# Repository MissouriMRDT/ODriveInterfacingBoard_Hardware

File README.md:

# ODriveInterfacingBoard_Hardware

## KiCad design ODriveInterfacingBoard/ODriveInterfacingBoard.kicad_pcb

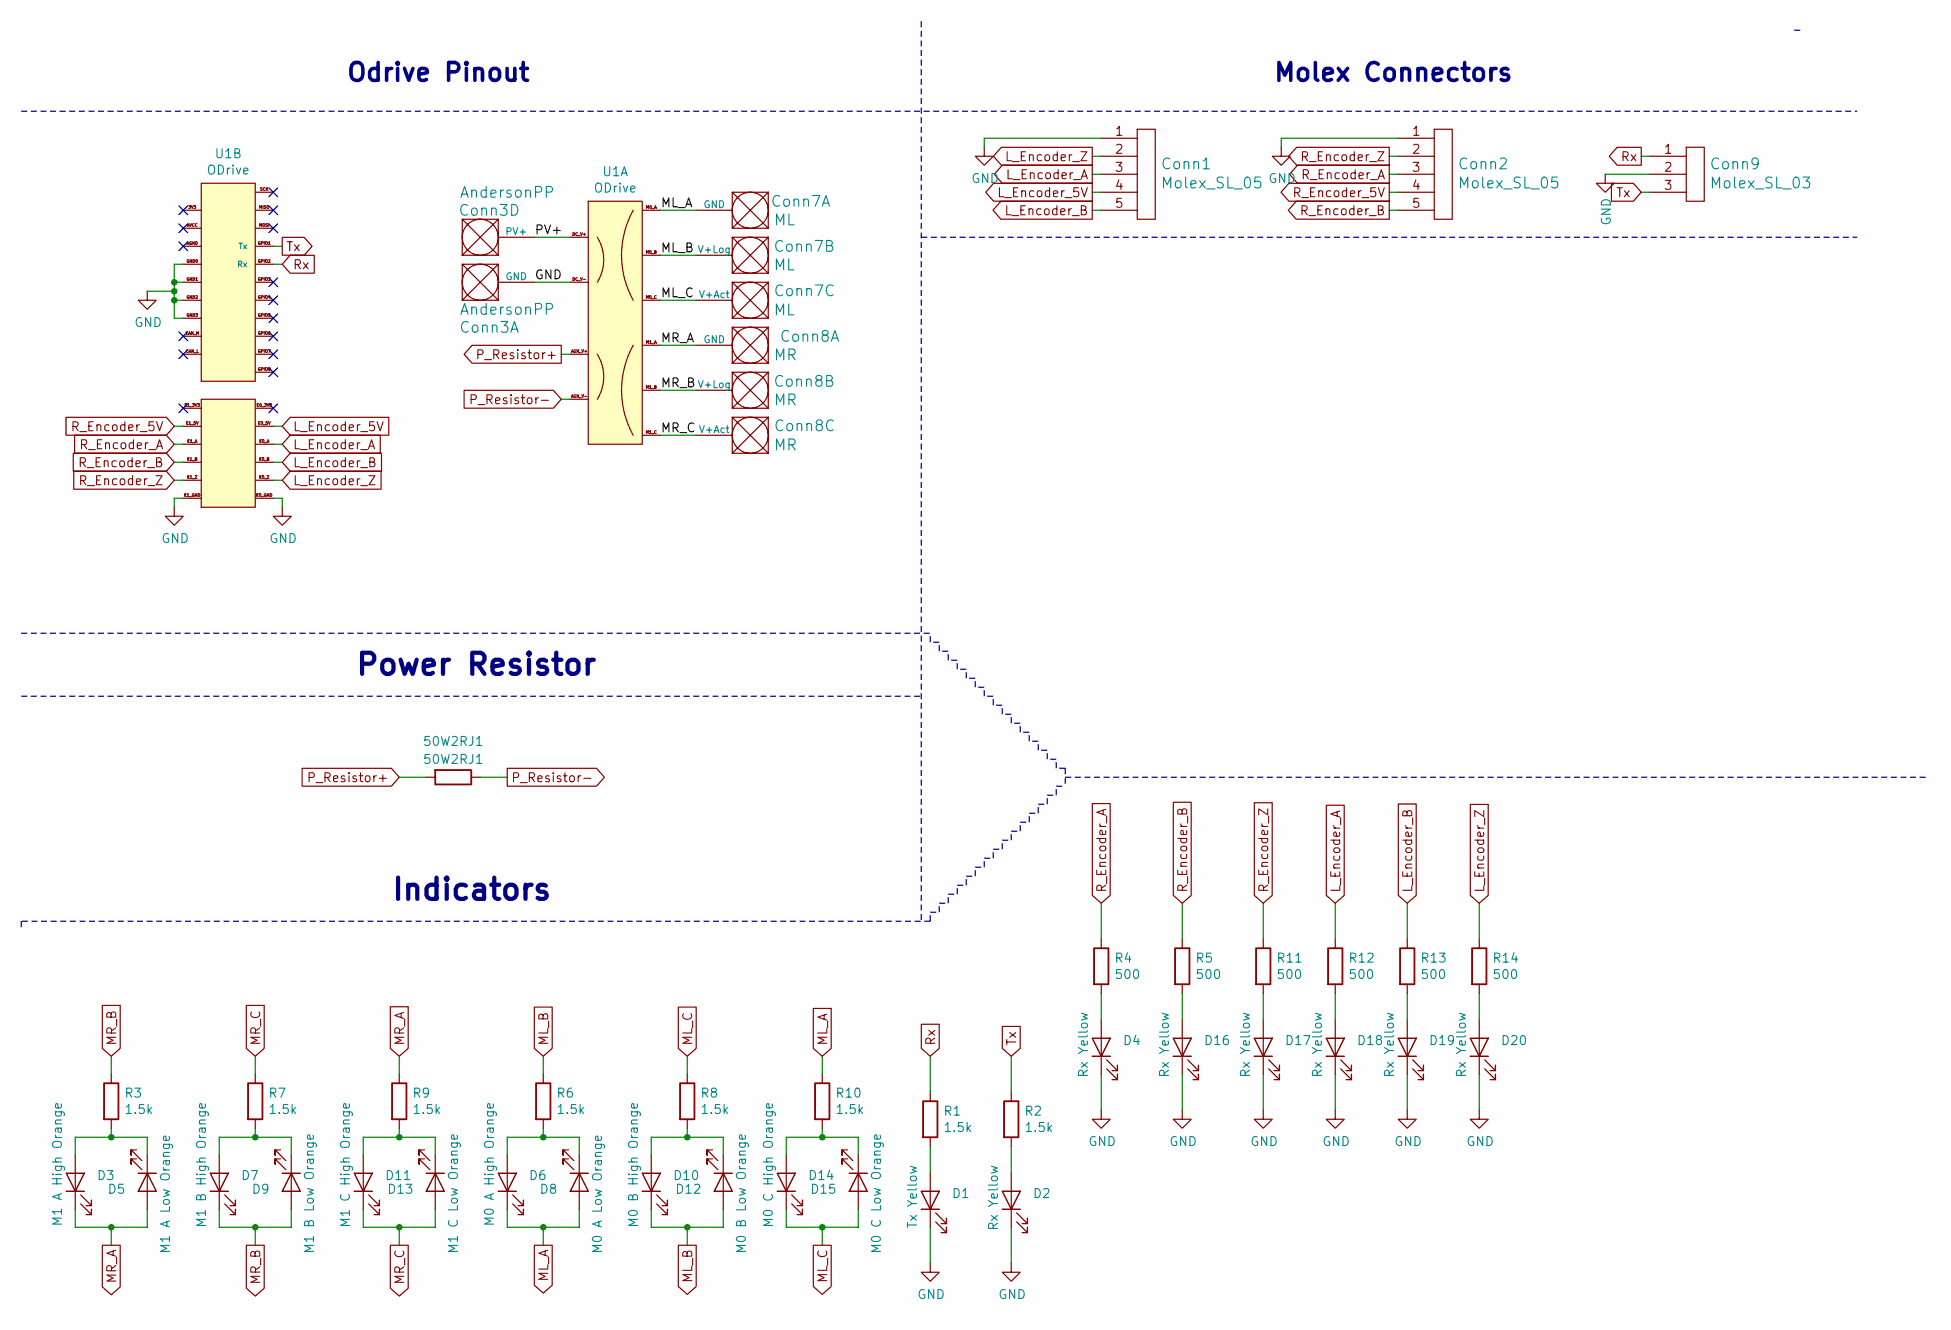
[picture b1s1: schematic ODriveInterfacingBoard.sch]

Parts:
50W2RJ1: 50W2RJ1; PowerResistorMounts
Conn1, Conn2: Molex_SL_05; MOLEX_SL_05_Horizontal
Conn3: AndersonPP; Anderson_2_Horizontal_Stacked
Conn7: ML; Anderson_3_Horizontal_Side_by_Side
Conn8: MR; Anderson_3_Horizontal_Side_by_Side
Conn9: Molex_SL_03; MOLEX_SL_03_Horizontal
D1: Tx Yellow; LED_0603_1608Metric_Pad1.05x0.95mm_HandSolder
D2, D4, D16, D17, D18, D19, D20: Rx Yellow; LED_0603_1608Metric_Pad1.05x0.95mm_HandSolder
D3: M1 A High Orange; LED_0603_1608Metric_Pad1.05x0.95mm_HandSolder
D5: M1 A Low Orange; LED_0603_1608Metric_Pad1.05x0.95mm_HandSolder
D6: M0 A High Orange; LED_0603_1608Metric_Pad1.05x0.95mm_HandSolder
D7: M1 B High Orange; LED_0603_1608Metric_Pad1.05x0.95mm_HandSolder
D8: M0 A Low Orange; LED_0603_1608Metric_Pad1.05x0.95mm_HandSolder
D9: M1 B Low Orange; LED_0603_1608Metric_Pad1.05x0.95mm_HandSolder
D10: M0 B High Orange; LED_0603_1608Metric_Pad1.05x0.95mm_HandSolder
D11: M1 C High Orange; LED_0603_1608Metric_Pad1.05x0.95mm_HandSolder
D12: M0 B Low Orange; LED_0603_1608Metric_Pad1.05x0.95mm_HandSolder
D13: M1 C Low Orange; LED_0603_1608Metric_Pad1.05x0.95mm_HandSolder
D14: M0 C High Orange; LED_0603_1608Metric_Pad1.05x0.95mm_HandSolder
D15: M0 C Low Orange; LED_0603_1608Metric_Pad1.05x0.95mm_HandSolder
R1, R2, R3, R6, R7, R8, R9, R10: 1.5k; R_0603_1608Metric_Pad1.05x0.95mm_HandSolder
R4, R5, R11, R12, R13, R14: 500; R_0603_1608Metric_Pad1.05x0.95mm_HandSolder
U1: ODrive; ODriveInterfacingBoard

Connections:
/PV+: Conn3.4 (PV+), U1.DC_V+
GND: Conn1.1, Conn2.1, Conn3.1 (GND), Conn9.2, D1.1 (K), D2.1 (K), D4.1 (K), D16.1 (K), D17.1 (K), D18.1 (K), D19.1 (K), D20.1 (K), U1.DC_V-, U1.E0_GND, U1.E1_GND, U1.GND0, U1.GND1, U1.GND2, U1.GND3
L_Encoder_5V: Conn1.4, U1.E0_5V
L_Encoder_A: Conn1.3, R12.1, U1.E0_A
L_Encoder_B: Conn1.5, R13.1, U1.E0_B
L_Encoder_Z: Conn1.2, R14.1, U1.E0_Z
ML_A: Conn7.1 (GND), D6.1 (K), D8.2 (A), R10.1, U1.M0_A
ML_B: Conn7.2 (V+Log), D10.1 (K), D12.2 (A), R6.1, U1.M0_B
ML_C: Conn7.3 (V+Act), D14.1 (K), D15.2 (A), R8.1, U1.M0_C
MR_A: Conn8.1 (GND), D3.1 (K), D5.2 (A), R9.1, U1.M1_A
MR_B: Conn8.2 (V+Log), D7.1 (K), D9.2 (A), R3.1, U1.M1_B
MR_C: Conn8.3 (V+Act), D11.1 (K), D13.2 (A), R7.1, U1.M1_C
unnamed: D1.2 (A), R1.2
unnamed: D2.2 (A), R2.2
unnamed: D3.2 (A), D5.1 (K), R3.2
unnamed: D4.2 (A), R4.2
unnamed: D6.2 (A), D8.1 (K), R6.2
unnamed: D7.2 (A), D9.1 (K), R7.2
unnamed: D10.2 (A), D12.1 (K), R8.2
unnamed: D11.2 (A), D13.1 (K), R9.2
unnamed: D14.2 (A), D15.1 (K), R10.2
unnamed: D16.2 (A), R5.2
unnamed: D17.2 (A), R11.2
unnamed: D18.2 (A), R12.2
unnamed: D19.2 (A), R13.2
unnamed: D20.2 (A), R14.2
P_Resistor+: 50W2RJ1.2, U1.AUX_V+
P_Resistor-: 50W2RJ1.1, U1.AUX_V-
R_Encoder_5V: Conn2.4, U1.E1_5V
R_Encoder_A: Conn2.3, R4.1, U1.E1_A
R_Encoder_B: Conn2.5, R5.1, U1.E1_B
R_Encoder_Z: Conn2.2, R11.1, U1.E1_Z
Rx: Conn9.1, R1.1, U1.GPIO2 (Rx)
Tx: Conn9.3, R2.1, U1.GPIO1 (Tx)

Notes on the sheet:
Odrive Pinout
Indicators
Power Resistor
Molex Connectors

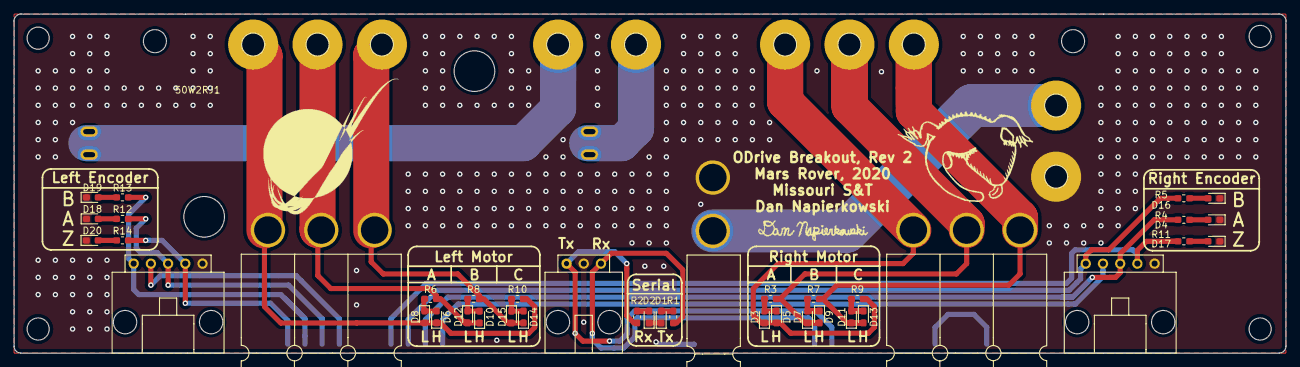
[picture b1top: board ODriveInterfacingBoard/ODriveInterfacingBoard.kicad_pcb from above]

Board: 2 copper layers, 187.7 x 50.0 mm, 42 parts (0 on the bottom side), 34 nets.

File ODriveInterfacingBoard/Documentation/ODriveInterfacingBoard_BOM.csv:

Id,Designator,Package,Designation,,Item Name,Item Number,,,Vendor,Quantity,Cost per Item,,,URL
1,U1,ODriveInterfacingBoard,ODrive,,Odrive V3.5,,,,Odrive Robotics,1,119,,,https://odriverobotics.com/shop/odrive-v35
2,50W2RJ1,PowerResistorMounts,50W2RJ1,,UNIVERSAL CLIP BOTTOM ENTRY,36-3577-ND,,,DigiKey,2,$0.22 ,,,https://www.digikey.com/product-detail/en/keystone-electroni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
3,"Conn4,Conn5,Conn6",MOLEX_SL_07_Horizontal,Molex_SL_07,,CONN HEADER R/A 7POS 2.54MM,WM4169-ND,,,DigiKey,3,$1.25 ,,,https://www.digikey.com/product-detail/en/molex-connector-co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
5,Conn1,MOLEX_SL_02_Horizontal,Molex_SL_02,,CONN HEADER R/A 2POS 2.54MM,WM4900-ND,,,DigiKey,1,$0.71 ,,,https://www.digikey.com/products/en?keywords=WM4900-ND
6,D1,LED_0603_1608Metric_Pad1.05x0.95mm_HandSolder,Tx Yellow,,LED YELLOW CLEAR SMD,160-1448-1-ND,,,Digikey,1,$0.31 ,,,https://www.Digikey.com/product-detail/en/lite-on-inc/LTST-C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
7,D2,LED_0603_1608Metric_Pad1.05x0.95mm_HandSolder,Rx Yellow,,LED YELLOW CLEAR SMD,160-1448-1-ND,,,Digikey,1,$0.31 ,,,https://www.Digikey.com/product-detail/en/lite-on-inc/LTST-C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
8,D3,LED_0603_1608Metric_Pad1.05x0.95mm_HandSolder,M1 A High Orange,,"LED ORANGE CLEAR SMD	",160-1445-1-ND,,,Digikey,1,$0.27 ,,,https://www.Digikey.com/product-detail/en/lite-on-inc/LTST-C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
9,D4,LED_0603_1608Metric_Pad1.05x0.95mm_HandSolder,3v3 Green,,LED GREEN CLEAR SMD,160-1446-1-ND,,,DigiKey,1,$0.29 ,,,https://www.digikey.com/product-detail/en/lite-on-inc/LTST-C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
10,D5,LED_0603_1608Metric_Pad1.05x0.95mm_HandSolder,M1 A Low Orange,,"LED ORANGE CLEAR SMD	",160-1445-1-ND,,,Digikey,1,$0.27 ,,,https://www.Digikey.com/product-detail/en/lite-on-inc/LTST-C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
11,D6,LED_0603_1608Metric_Pad1.05x0.95mm_HandSolder,M0 A High Orange,,"LED ORANGE CLEAR SMD	",160-1445-1-ND,,,Digikey,1,$0.27 ,,,https://www.Digikey.com/product-detail/en/lite-on-inc/LTST-C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
12,D7,LED_0603_1608Metric_Pad1.05x0.95mm_HandSolder,M1 B High Orange,,"LED ORANGE CLEAR SMD	",160-1445-1-ND,,,Digikey,1,$0.27 ,,,https://www.Digikey.com/product-detail/en/lite-on-inc/LTST-C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
13,D8,LED_0603_1608Metric_Pad1.05x0.95mm_HandSolder,M0 A Low Orange,,"LED ORANGE CLEAR SMD	",160-1445-1-ND,,,Digikey,1,$0.27 ,,,https://www.Digikey.com/product-detail/en/lite-on-inc/LTST-C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
14,D9,LED_0603_1608Metric_Pad1.05x0.95mm_HandSolder,M1 B Low Orange,,"LED ORANGE CLEAR SMD	",160-1445-1-ND,,,Digikey,1,$0.27 ,,,https://www.Digikey.com/product-detail/en/lite-on-inc/LTST-C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
15,D10,LED_0603_1608Metric_Pad1.05x0.95mm_HandSolder,M0 B High Orange,,"LED ORANGE CLEAR SMD	",160-1445-1-ND,,,Digikey,1,$0.27 ,,,https://www.Digikey.com/product-detail/en/lite-on-inc/LTST-C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
16,D11,LED_0603_1608Metric_Pad1.05x0.95mm_HandSolder,M1 C High Orange,,"LED ORANGE CLEAR SMD	",160-1445-1-ND,,,Digikey,1,$0.27 ,,,https://www.Digikey.com/product-detail/en/lite-on-inc/LTST-C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
17,D12,LED_0603_1608Metric_Pad1.05x0.95mm_HandSolder,M0 B Low Orange,,"LED ORANGE CLEAR SMD	",160-1445-1-ND,,,Digikey,1,$0.27 ,,,https://www.Digikey.com/product-detail/en/lite-on-inc/LTST-C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
18,D13,LED_0603_1608Metric_Pad1.05x0.95mm_HandSolder,M1 C Low Orange,,"LED ORANGE CLEAR SMD	",160-1445-1-ND,,,Digikey,1,$0.27 ,,,https://www.Digikey.com/product-detail/en/lite-on-inc/LTST-C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
19,D14,LED_0603_1608Metric_Pad1.05x0.95mm_HandSolder,M0 C High Orange,,"LED ORANGE CLEAR SMD	",160-1445-1-ND,,,Digikey,1,$0.27 ,,,https://www.Digikey.com/product-detail/en/lite-on-inc/LTST-C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
20,D15,LED_0603_1608Metric_Pad1.05x0.95mm_HandSolder,M0 C Low Orange,,"LED ORANGE CLEAR SMD	",160-1445-1-ND,,,Digikey,1,$0.27 ,,,https://www.Digikey.com/product-detail/en/lite-on-inc/LTST-C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
21,"R1,R2,R4,R3,R6,R7,R10,R11,R14",R_0603_1608Metric_Pad1.05x0.95mm_HandSolder,1.5k,,RES SMD 1.5K OHM 5% 1/4W 0603,"	RHM1.5KDCT-ND",,,Digikey,9,$0.10 ,,,https://www.Digikey.com/product-detail/en/rohm-semiconductor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
22,"Conn7, Conn8",Anderson_3_Horizontal_Side_by_Side,M0_A,,PCB Horizontal Bottom Contact,1336G1,,,Powerwerx,6,$0.53 ,,,https://powerwerx.com/anderson-1336g1-printed-circuit-board-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
,,,,,Yellow Housing,1327G16,,,Powerwerx,2,$0.39 ,,,https://powerwerx.com/anderson-powerpole-colored-housings
,,,,,Red Housing,1327,,,Powerwerx,2,$0.37 ,,,https://powerwerx.com/anderson-powerpole-colored-housings
,,,,,Blue Housing,1327G8,,,Powerwerx,2,$0.39 ,,,https://powerwerx.com/anderson-powerpole-colored-housings
24,C1,C_0603_1608Metric_Pad1.05x0.95mm_HandSolder,.1u,,CAP CER 0.1UF 16V X7R 0603,"1276-1005-1-ND	",,,Digikey,1,$0.10 ,,,https://www.digikey.com/product-detail/en/samsung-electro-me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
25,Conn3,Anderson_2_Horizontal_Stacked,AndersonPP,,PCB Horizontal Bottom Contact,1336G1,,,Powerwerx,1,$0.53 ,,,https://powerwerx.com/anderson-1336g1-printed-circuit-board-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
,,,,,PCB Horizontal Top Contact,1337G1 ,,,Powerwerx,1,$0.56 ,,,https://powerwerx.com/anderson-1337g1-printed-circuit-board-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
,,,,,Red Housing,1327,,,Powerwerx,1,$0.37 ,,,https://powerwerx.com/anderson-powerpole-colored-housings
,,,,,Black Housing,1327G6,,,Powerwerx,1,$0.37 ,,,https://powerwerx.com/anderson-powerpole-colored-housings
26,"R16,R17",R_0603_1608Metric_Pad1.05x0.95mm_HandSolder,0,,RES 0 OHM JUMPER 1/10W 0603,RMCF0603ZT0R00CT-ND,,,DigiKey,2,$0.10 ,,,https://www.digikey.com/product-detail/en/stackpole-electron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
27,U2,SOIC-8_3.9x4.9mm_P1.27mm,MAX3077E,,IC TXRX RS485/422 8-SOIC,MAX3077EESA+-ND,,,Digikey,3,3.57,,,https://www.digikey.com/product-detail/en/maxim-integrated/M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
28,R18,R_0603_1608Metric_Pad1.05x0.95mm_HandSolder,120,,RES SMD 120 OHM 5% 1/4W 0603,RHM120DCT-ND,,,DigiKey,1,$0.10 ,,,https://www.digikey.com/product-detail/en/rohm-semiconductor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
29,Conn2,MOLEX_SL_05_Vertical,Molex_SL_05,,CONN HEADER VERT 5POS 2.54MM,WM4827-ND,,,DigiKey,1,$1.11 ,,,https://www.digikey.com/product-detail/en/molex-llc/07054300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
30,Conn13,MOLEX_SL_09_Vertical,Molex_SL_09,,CONN HEADER VERT 9POS 2.54MM,WM4831-ND,,,DigiKey,1,$1.43 ,,,https://www.digikey.com/product-detail/en/molex-llc/07054300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
31,Conn9,MOLEX_SL_03_Horizontal,Molex_SL_03,,CONN HEADER R/A 3POS 2.54MM,WM4901-ND,,,DigiKey,1,$1.12 ,,,https://www.digikey.com/products/en?keywords=WM4901-ND
32,Conn10,MOLEX_SL_05_Horizontal,Molex_SL_05,,CONN HEADER R/A 5POS 2.54MM,WM4903-ND,,,DigiKey,1,$1.21 ,,,https://www.digikey.com/products/en?keywords=WM4903-ND
33,,Board spacers,,,"HEX STANDOFF #4-40 ALUMINUM 1/2""",1772-1098-ND,,,DigiKey,4,$0.47 ,,,https://www.digikey.com/product-detail/en/raf-electronic-har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

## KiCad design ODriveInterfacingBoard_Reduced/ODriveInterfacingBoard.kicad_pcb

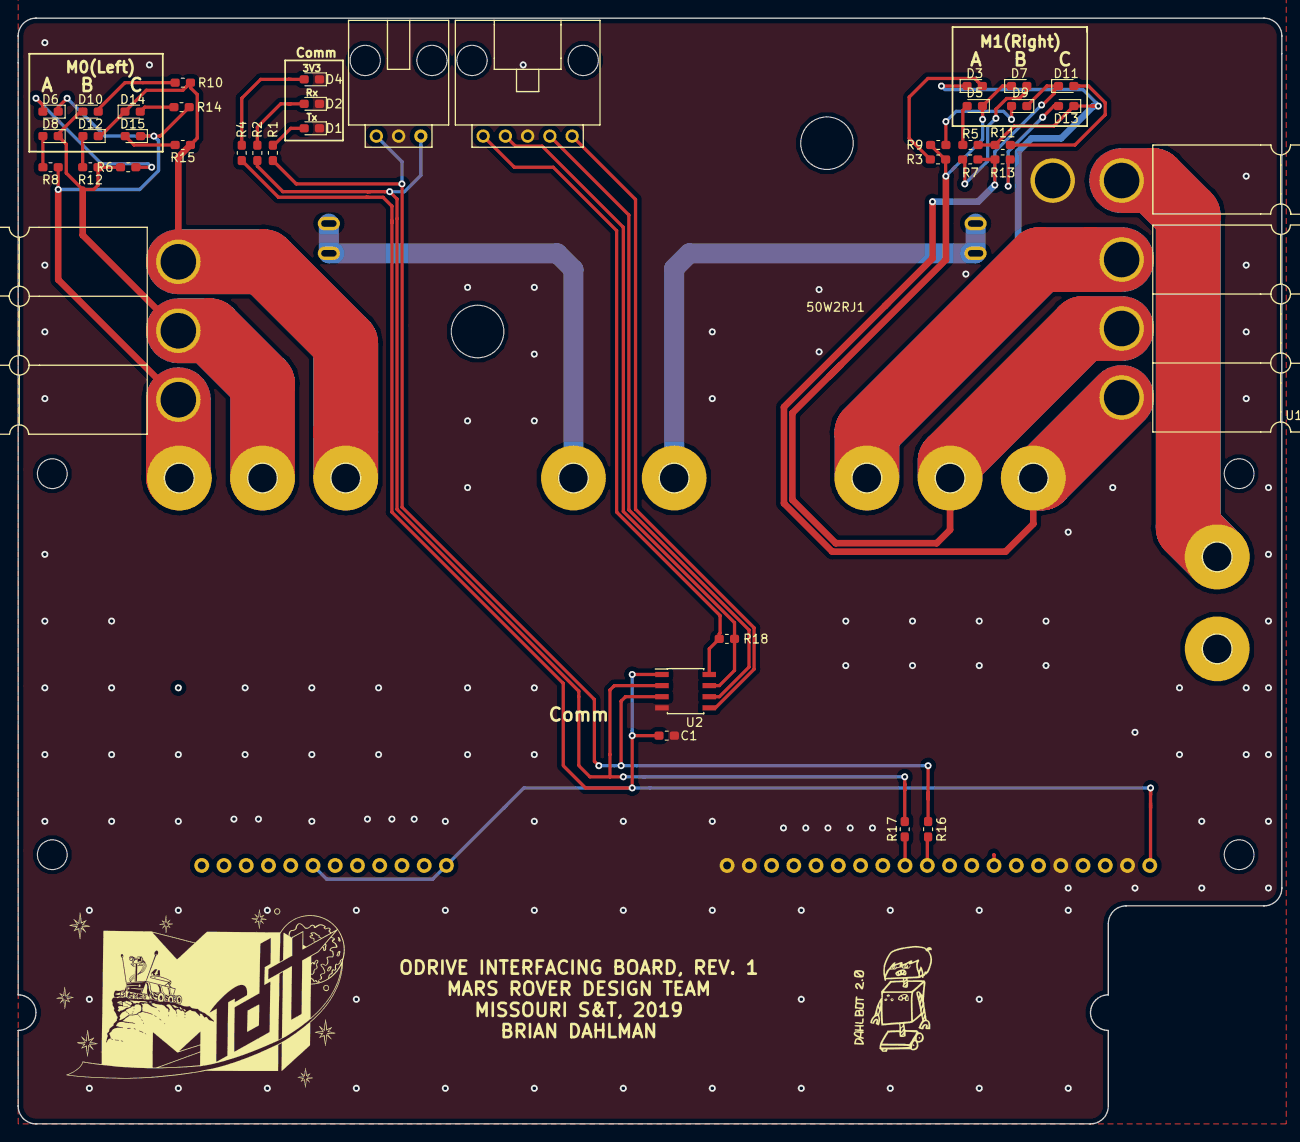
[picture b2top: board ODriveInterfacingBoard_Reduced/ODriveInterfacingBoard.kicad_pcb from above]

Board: 2 copper layers, 144.3 x 126.2 mm, 42 parts (0 on the bottom side), 29 nets.

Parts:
50W2RJ1: 50W2RJ1; PowerResistorMounts
C1: .1u; C_0603_1608Metric_Pad1.05x0.95mm_HandSolder
Conn3: AndersonPP; Anderson_2_Horizontal_Stacked
Conn7: M0_A; Anderson_3_Horizontal_Side_by_Side
Conn8: M1_A; Anderson_3_Horizontal_Side_by_Side
Conn9: Molex_SL_03; MOLEX_SL_03_Horizontal
Conn10: Molex_SL_05; MOLEX_SL_05_Horizontal
D1: Tx Yellow; LED_0603_1608Metric_Pad1.05x0.95mm_HandSolder
D2: Rx Yellow; LED_0603_1608Metric_Pad1.05x0.95mm_HandSolder
D3: M1 A High Orange; LED_0603_1608Metric_Pad1.05x0.95mm_HandSolder
D4: 3v3 Green; LED_0603_1608Metric_Pad1.05x0.95mm_HandSolder
D5: M1 A Low Orange; LED_0603_1608Metric_Pad1.05x0.95mm_HandSolder
D6: M0 A High Orange; LED_0603_1608Metric_Pad1.05x0.95mm_HandSolder
D7: M1 B High Orange; LED_0603_1608Metric_Pad1.05x0.95mm_HandSolder
D8: M0 A Low Orange; LED_0603_1608Metric_Pad1.05x0.95mm_HandSolder
D9: M1 B Low Orange; LED_0603_1608Metric_Pad1.05x0.95mm_HandSolder
D10: M0 B High Orange; LED_0603_1608Metric_Pad1.05x0.95mm_HandSolder
D11: M1 C High Orange; LED_0603_1608Metric_Pad1.05x0.95mm_HandSolder
D12: M0 B Low Orange; LED_0603_1608Metric_Pad1.05x0.95mm_HandSolder
D13: M1 C Low Orange; LED_0603_1608Metric_Pad1.05x0.95mm_HandSolder
D14: M0 C High Orange; LED_0603_1608Metric_Pad1.05x0.95mm_HandSolder
D15: M0 C Low Orange; LED_0603_1608Metric_Pad1.05x0.95mm_HandSolder
R1, R2, R3, R4, R5, R6, R7, R8, R9, R10, R11, R12, R13, R14, R15: 1.5k; R_0603_1608Metric_Pad1.05x0.95mm_HandSolder
R16, R17: 0; R_0603_1608Metric_Pad1.05x0.95mm_HandSolder
R18: 120; R_0603_1608Metric_Pad1.05x0.95mm_HandSolder
U1: ODrive; ODriveInterfacingBoard
U2: MAX3077E; SOIC-8_3.9x4.9mm_P1.27mm

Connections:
+3V3: C1.1, R4.1, U1.3V3, U2.1
/A: Conn10.1, R18.2, U2.8
/B: Conn10.2, R18.1, U2.7
/Y: Conn10.5, U2.5
/Z: Conn10.4, U2.6
GND: C1.2, Conn3.4, Conn9.2, Conn10.3, D1.1, D2.1, D4.1, U1.GND0, U1.GND1, U1.GND2, U1.GND3, U2.4
M0_A: Conn7.3, D6.1, D8.2, R14.1, R15.2, U1.M0_A
M0_B: Conn7.2, D10.1, D12.2, R6.1, R8.2, U1.M0_B
M0_C: Conn7.1, D14.1, D15.2, R10.1, R12.2, U1.M0_C
M1_A: Conn8.3, D3.1, D5.2, R11.1, R13.2, U1.M1_A
M1_B: Conn8.2, D7.1, D9.2, R3.1, R5.2, U1.M1_B
M1_C: Conn8.1, D11.1, D13.2, R7.1, R9.2, U1.M1_C
unnamed: D1.2, R1.2
unnamed: D2.2, R2.2
unnamed: D3.2, R3.2
unnamed: D4.2, R4.2
unnamed: D5.1, R5.1
unnamed: D6.2, R6.2
unnamed: D7.2, R7.2
unnamed: D8.1, R8.1
unnamed: D9.1, R9.1
unnamed: D10.2, R10.2
unnamed: D11.2, R11.2
unnamed: D12.1, R12.1
unnamed: D13.1, R13.1
unnamed: D14.2, R14.2
unnamed: D15.1, R15.1
Rx: Conn9.3, R17.1, R17.2, U1.GPIO2, U2.2
Tx: Conn9.1, R16.1, R16.2, U1.GPIO1, U2.3

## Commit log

2019-02-24 finished teh schematic and started the layout
2019-02-24 started the ODrive footprint
2019-03-02 footprint progress
2019-03-02 finished footprints started layout
2019-03-02 power traces and hghlevel layout
2019-03-02 high level layout
2019-03-02 minor changes
2019-03-03 footprints made for resistor and odrive. Added IC to schematic
2019-03-04 finished traces of everything except LEDs
2019-03-04 via stitching added
2019-03-05 Added LEDs for comm and Low Motor Phases
2019-03-05 ADDED SILKSCREEN
2019-03-05 Made LEDs in a Delta Configuration
2019-03-05 Modified LED resistor order
2019-03-05 Fixed LED traces
2019-03-05 Re did traces
2019-03-05 Layout made, functional but needs cleaning up
2019-03-05 Finalized silkscreen
2019-03-05 Minor Silkscreen changes
2019-03-05 Fixed Tx Rx issue
2019-03-05 Fixed Serial tx rx wiring
2019-03-05 created Gerbs
2019-03-05 Added full board files
2019-03-05 created step file
2019-03-11 added bom
2019-03-11 added the board spacers to bom file
2019-04-04 started reworking the leds
2019-04-04 led arranging
2019-04-04 schematic work
2019-04-04 leds almost done
2019-04-04 Finished the layout.
2019-04-05 finished the via stitching. ready to make gerbs
2019-04-05 finished rev2
2019-04-05 generated gerbs & BOM
2019-12-02 worked on schematic
2019-12-03 blahblah I pushed
2019-12-03 whoops
2019-12-04 I pushed :+1: :eggplant: :eggplant: :eggplant: :eggplant: :eggplant: :eggplant: :eggplant: :eggplant: :eggplant:
2019-12-04 :eggplant: :eggplant: Just Need Silks
2019-12-04 :eggplant: :eggplant: Done
2019-12-04 Eggplant Emoji
2019-12-06 added silks
2019-12-07 vias and shit
2019-12-07 lmao
2019-12-07 Just need silks and vias, babam
2019-12-09 https://www.youtube.com/watch?v=dQw4w9WgXcQ
2019-12-15 Austin is hitler, confirmed
2019-12-15 whoops this one
2020-01-21 deleted because merge conflicts
2020-01-21 Revert "deleted because merge conflicts"
    This reverts commit 3284f96c56f59d0e9095026fda857c192b74f541.
2020-02-06 Fixed Silks, Changed rev number to 2
2020-02-06 added silks so they could feel like they did their job
2020-02-26 Added Gerbs
2020-03-03 Genreated new gerbs and changed silkscreenb
2020-10-05 Added Usb connectors in schematic
    USB to USB to USB to USB!!!!
2020-10-15 Post - Review
